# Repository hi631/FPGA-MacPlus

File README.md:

Make MacPlus  with FPGA

https://github.com/hi631/FPGA-MacPlus.git

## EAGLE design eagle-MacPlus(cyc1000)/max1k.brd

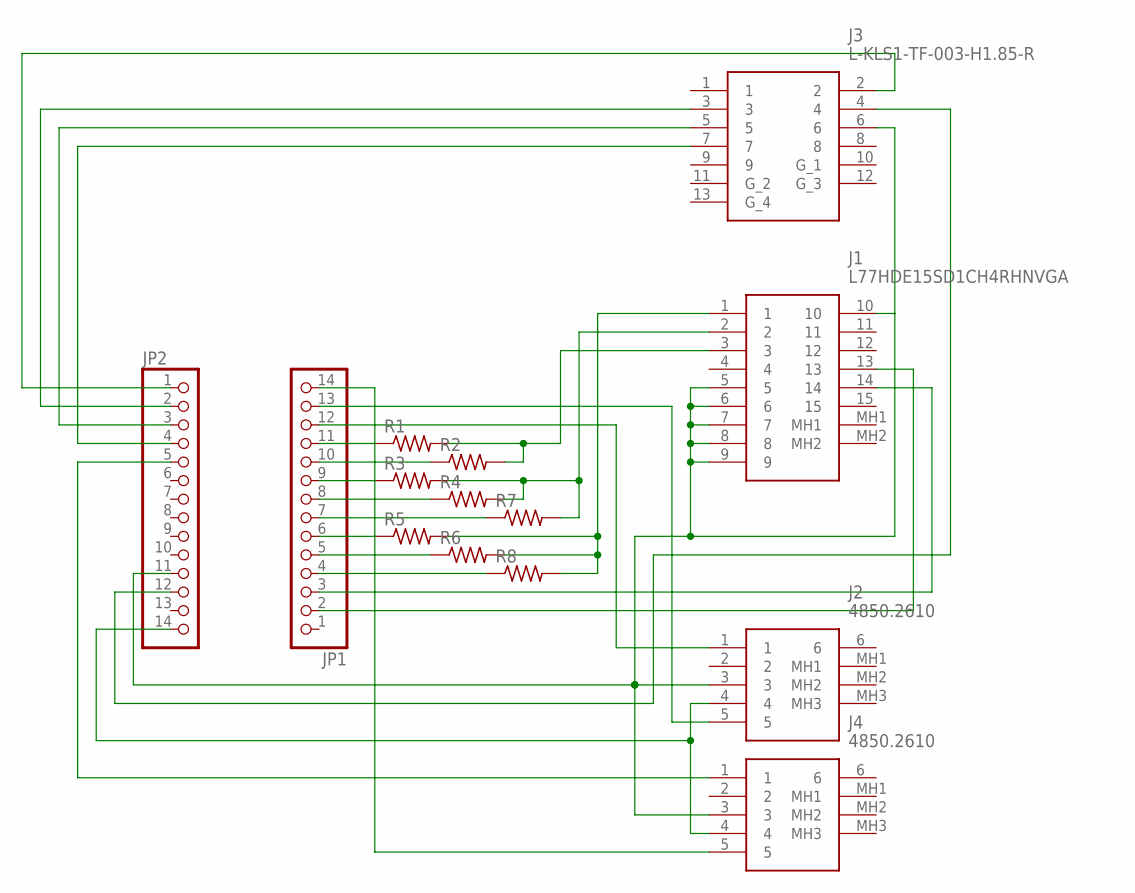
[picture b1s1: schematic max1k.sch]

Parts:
J1: L77HDE15SD1CH4RHNVGA
J2, J4: 4850.2610; 48502610
J3: L-KLS1-TF-003-H1.85-R
JP1, JP2: PINHD-1X14-CB; 1X14-CB
R1, R2, R3, R4, R5, R6, R7, R8: R-US_R0805; R0805

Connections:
GND: J1.5, J1.6, J1.7, J1.8, J1.9, J1.10, J2.3, J3.6, J4.3, JP2.11
unnamed: J1.13, JP1.2
unnamed: J1.14, JP1.3
unnamed: JP1.11, R1.1
unnamed: JP1.10, R2.1
unnamed: JP1.9, R3.1
unnamed: JP1.8, R4.1
unnamed: JP1.7, R7.1
unnamed: JP1.6, R5.1
unnamed: JP1.5, R6.1
unnamed: JP1.4, R8.1
unnamed: J1.3, R1.2, R2.2
unnamed: J1.2, R3.2, R4.2, R7.2
unnamed: J1.1, R5.2, R6.2, R8.2
unnamed: J3.4, JP2.12
unnamed: J4.5, JP1.14
unnamed: J2.1, JP1.12
unnamed: J3.5, JP2.3
unnamed: J3.3, JP2.2
unnamed: J4.1, JP2.5
unnamed: J3.7, JP2.4
unnamed: J2.5, JP1.13
unnamed: J2.4, J4.4, JP2.14
unnamed: J3.2, JP2.1

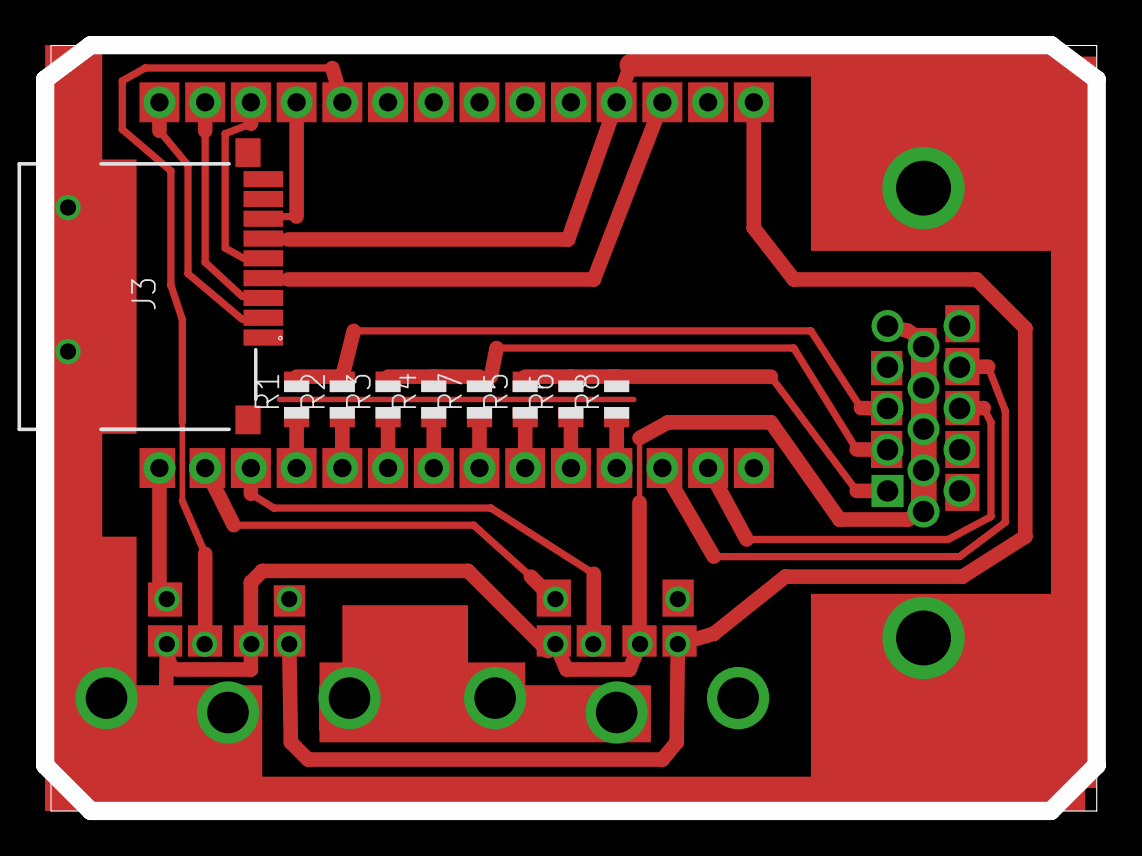
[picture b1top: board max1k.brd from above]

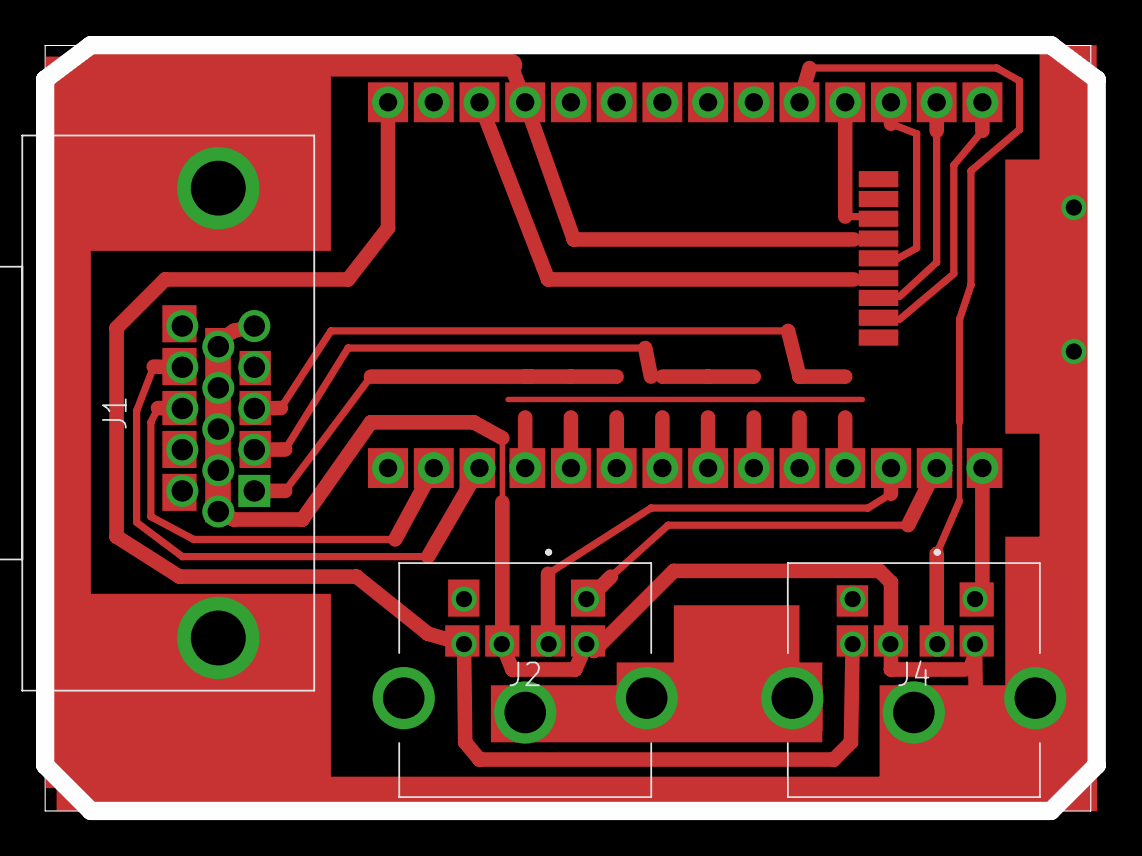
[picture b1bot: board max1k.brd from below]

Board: 2 copper layers, 58.4 x 42.5 mm, 14 parts (3 on the bottom side), 24 nets.
